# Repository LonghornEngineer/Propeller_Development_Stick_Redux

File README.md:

***
###Propeller_Development_Stick_Redux
***
**Tiny development board based on the Parallax Propeller.**

More information can be found on the [Propeller Development Stick project page](http://longhornengineer.com/projects/pcb/propeller-development-stick-redux/).

Board Files are for Cadsoft Eagle V6.0+

***
**License Information**

This project is under the [Creative Commons Attribution-ShareAlike 4.0 International License](LICENSE.md). These files are provided with no warranty and should be used at your own risk. 

***

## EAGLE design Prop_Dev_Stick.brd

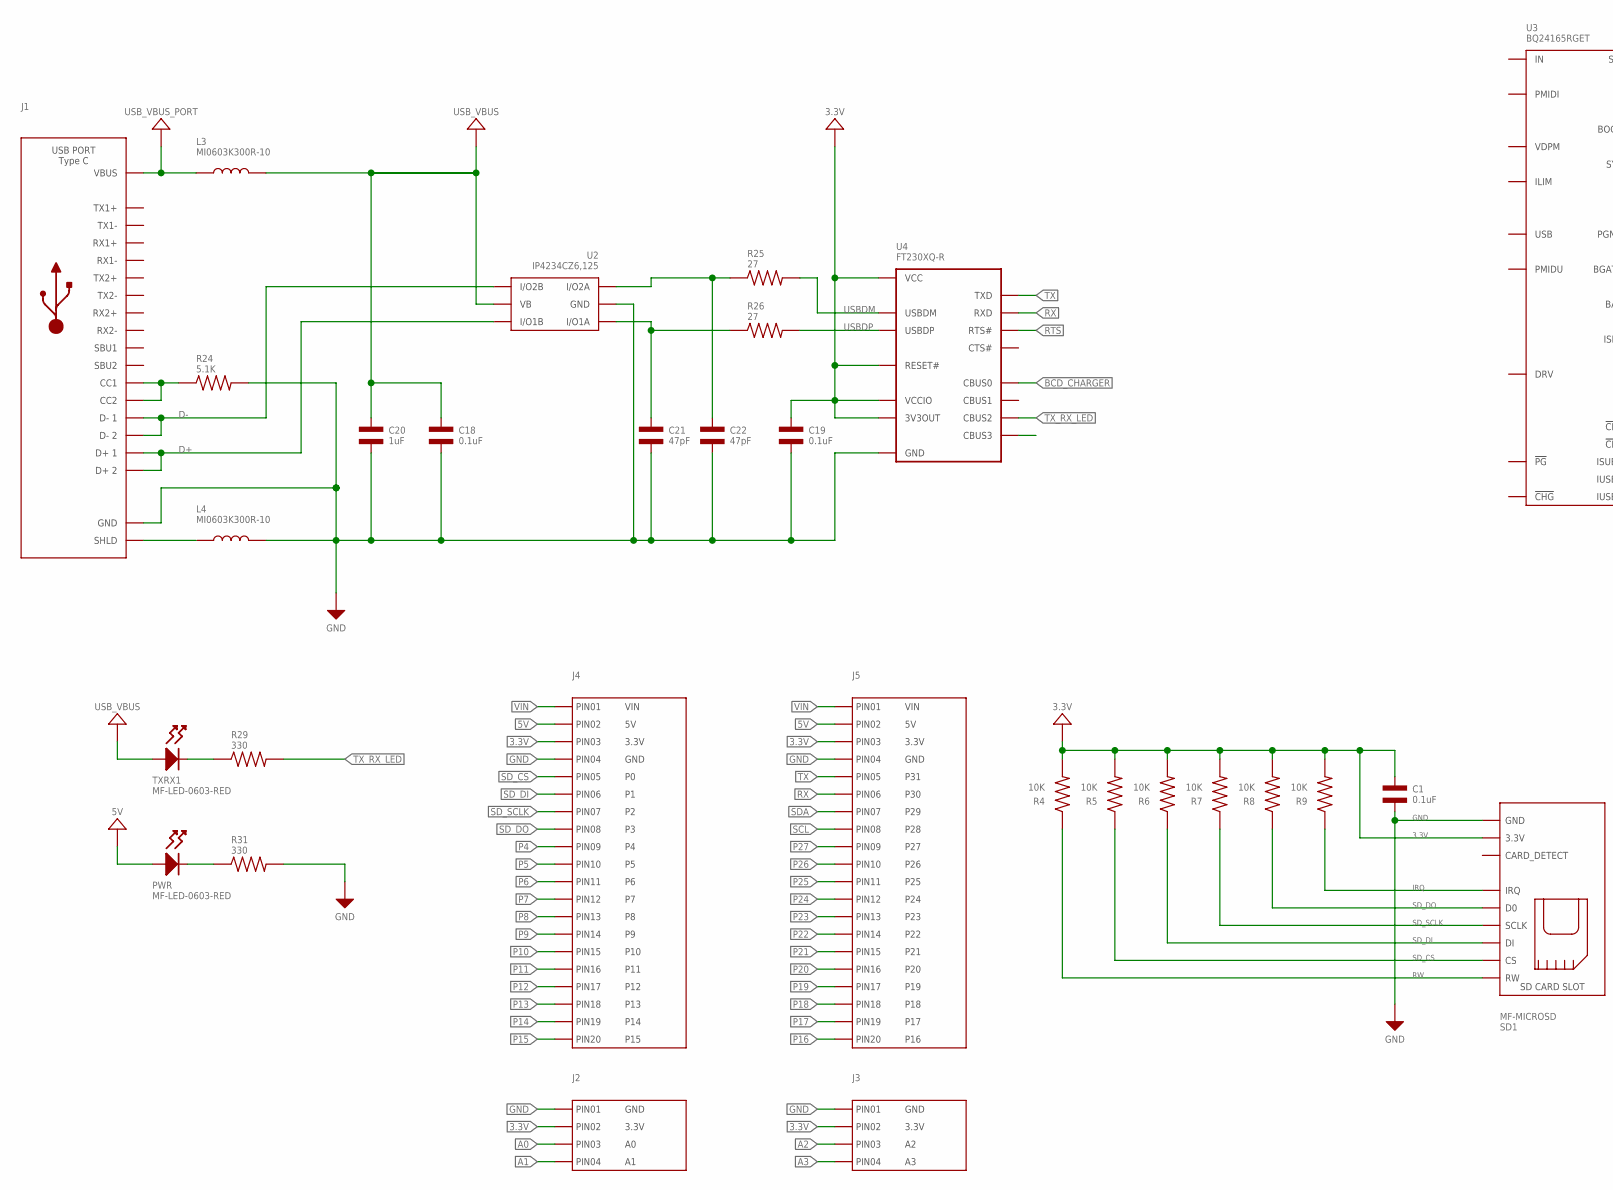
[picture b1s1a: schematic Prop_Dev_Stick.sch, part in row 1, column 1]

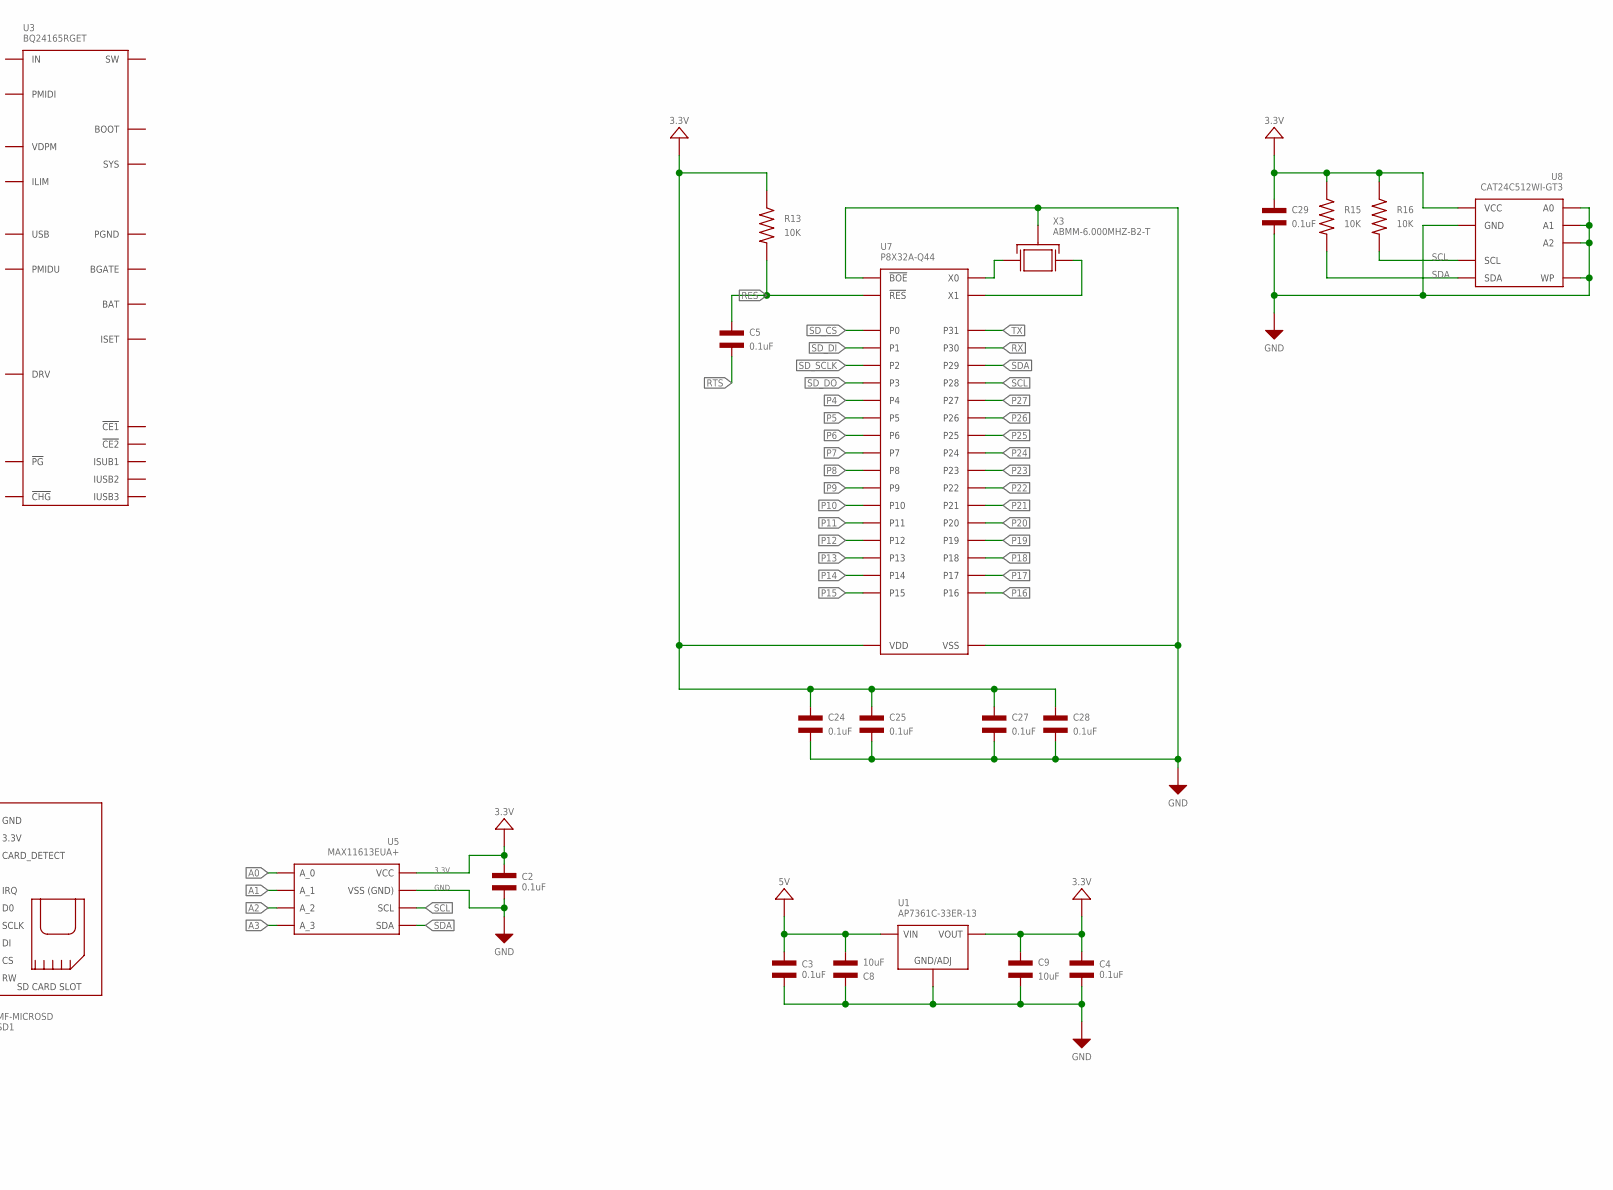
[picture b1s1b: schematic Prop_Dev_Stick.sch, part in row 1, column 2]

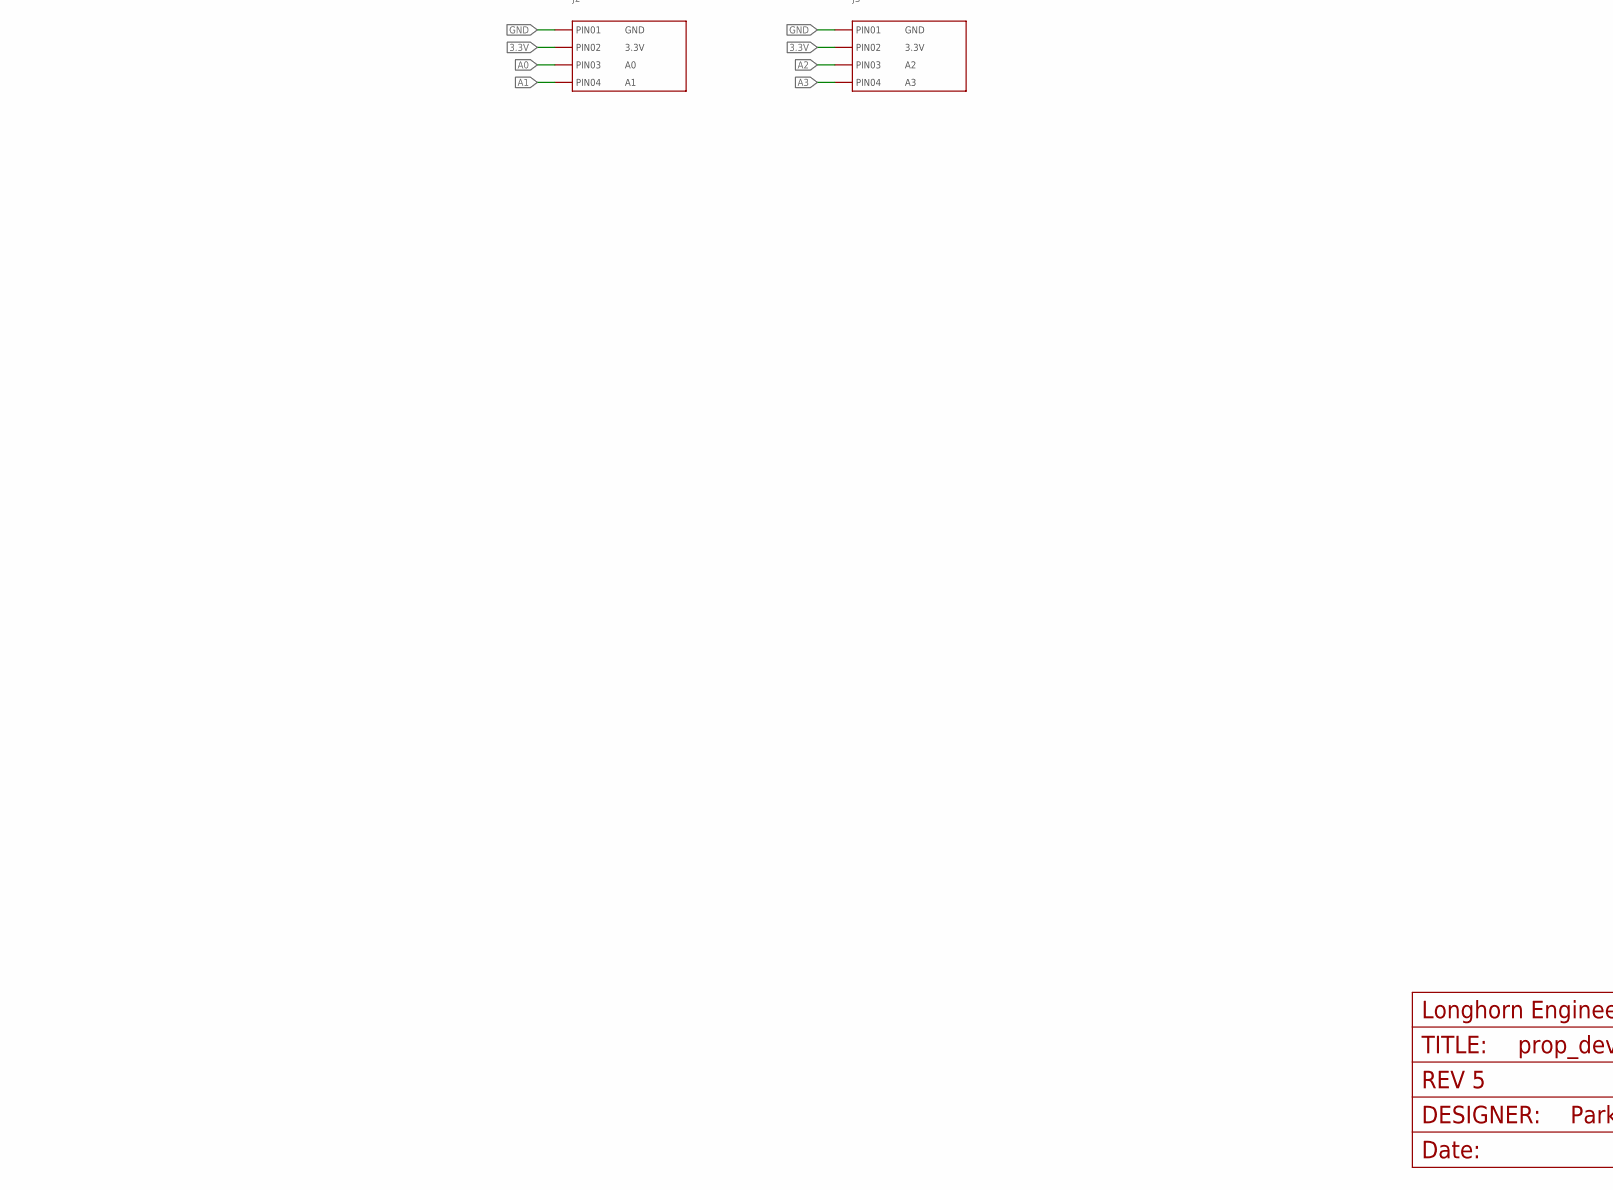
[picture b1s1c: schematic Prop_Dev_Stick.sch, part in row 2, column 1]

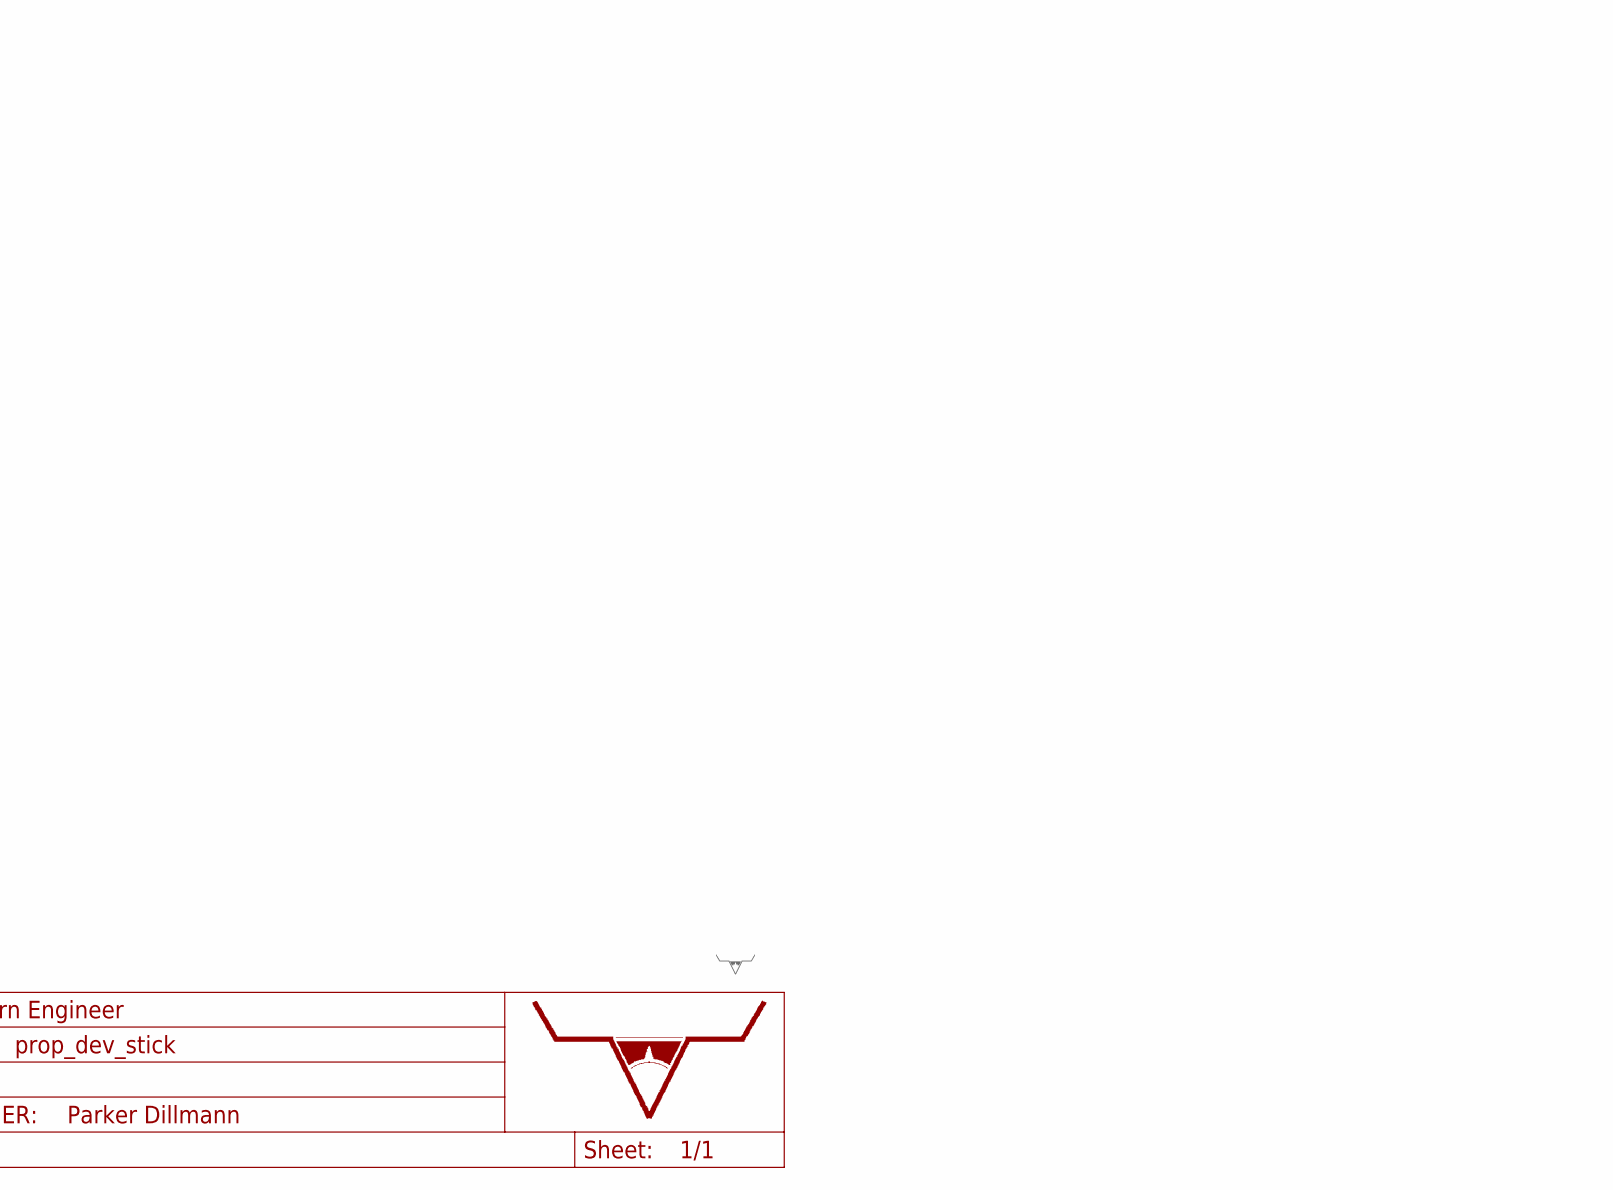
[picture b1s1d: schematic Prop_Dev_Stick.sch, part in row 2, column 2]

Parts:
C1, C2, C3, C4, C18, C19: 0.1uF; C0603
C5, C24, C25, C27, C28, C29: 0.1uF; C0402; MPN MF-CAP-0603-0.1uF
C8, C9: 10uF; C1206
C20: 1uF; C0603
C21, C22: 47pF; C0603
J1: USB_TYPE-C_105450-0101; 105450-0101
J2, J3: CON_01X04_2.54MM_PIN_HEADER; 2.54MM_01X04_PIN_HEADER
J4, J5: CON_01X20_2.54MM_PIN_HEADER; 2.54MM_01X20_PIN_HEADER
L3, L4: MI0603K300R-10; L0603
PWR: MF-LED-0603-RED; LED0603
R4, R5, R6, R7, R8, R9: 10K; R0603
R13: 10K; R0402; MPN MF-RES-0805-10K
R15, R16: 10K; R0402; MPN MF-RES-0603-10K
R24: 5.1K; R0603
R25, R26: 27; R0603
R29, R31: 330; R0402
SD1: MF-MICROSD
TXRX1: MF-LED-0603-RED; LED0603
U1: AP7361C-33ER-13; ADP3338_SOT-223-3
U2: IP4234CZ6,125; IP4234CZ6_SOT-457-6
U3: BQ24165RGET; BQ24165_QFN-24
U4: FT230XQ-R; FT230X_QFN-16
U5: MAX11613EUA+; MAX11613_UMAX-8
U7: P8X32A-Q44; P8X32A_QFN-44; MPN P8X32A-Q44
U8: CAT24C512WI-GT3; SOIC-8_W; MPN CAT24C512WI-GT3
U$1: LHE_FRAME
U$2: LHE_LOGOLHE_LOGO; LHE_LOGO
X3: ABMM-6.000MHZ-B2-T; 7MMX5MM; MPN ABMM-6.000MHZ-B2-T

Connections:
3.3V: C1.P$1, C2.P$1, C4.P$1, C9.P$1, C19.P$1, C24.P$1, C25.P$1, C27.P$1, C28.P$1, C29.P$1, J2.2, J3.2, J4.3, J5.3, R4.P$2, R5.P$2, R6.P$2, R7.P$2, R8.P$2, R9.P$2, R13.P$1, R15.P$1, R16.P$1, SD1.PIN4 (3.3V), U1.2 (OUT), U1.PAD (OUT), U4.1 (VCCIO), U4.8 (3V3OUT), U4.9 (RESET#), U4.10 (VCC), U5.P$8 (VCC), U7.8 (VDD), U7.18 (VDD), U7.30 (VDD), U7.40 (VDD), U8.8 (VCC)
5V: C3.P$1, C8.P$2, J4.2, J5.2, PWR.ANODE, U1.3 (IN)
A0: J2.3, U5.P$1 (A_0)
A1: J2.4, U5.P$2 (A_1)
A2: J3.3, U5.P$3 (A_2)
A3: J3.4, U5.P$4 (A_3)
BCD_CHARGER: U4.12 (CBUS0)
CC1/1: J1.A5 (CC1), J1.B5 (CC2), R24.P$1
D+: J1.A6 (D+1), J1.B6 (D+2), U2.3 (I/O1B)
D-: J1.A7 (D-1), J1.B7 (D-2), U2.4 (I/O2B)
GND: C1.P$2, C2.P$2, C3.P$2, C4.P$2, C8.P$1, C9.P$2, C18.P$2, C19.P$2, C20.P$2, C21.P$2, C22.P$2, C24.P$2, C25.P$2, C27.P$2, C28.P$2, C29.P$2, J1.A1 (GND), J1.A12 (GND), J1.B1 (GND), J1.B12 (GND), J2.1, J3.1, J4.4, J5.4, L4.P$2, R24.P$2, R31.P$2, SD1.G0 (GND), SD1.G1 (GND), SD1.PIN6 (GND), U1.1 (GND), U2.2 (GND), U4.3 (GND), U4.13 (GND), U4.PAD (GND), U5.P$7 (GND), U7.5 (VSS), U7.6 (!BOE), U7.17 (VSS), U7.27 (VSS), U7.39 (VSS), U8.1 (A0), U8.2 (A1), U8.3 (A2), U8.4 (GND), U8.7 (WP), X3.P$2 (GND), X3.P$4 (GND)
IRQ: R9.P$1, SD1.PIN8 (IRQ)
unnamed: R29.P$1, TXRX1.CATHODE
unnamed: PWR.CATHODE, R31.P$1
unnamed: J1.S_T1 (SHLD), J1.S_T2 (SHLD), J1.S_T3 (SHLD), J1.S_T4 (SHLD), L4.P$1
unnamed: C21.P$1, R26.P$1, U2.1 (I/O1A)
unnamed: C22.P$1, R25.P$1, U2.6 (I/O2A)
P4: J4.9, U7.1 (P4)
P5: J4.10, U7.2 (P5)
P6: J4.11, U7.3 (P6)
P7: J4.12, U7.4 (P7)
P8: J4.13, U7.9 (P8)
P9: J4.14, U7.10 (P9)
P10: J4.15, U7.11 (P10)
P11: J4.16, U7.12 (P11)
P12: J4.17, U7.13 (P12)
P13: J4.18, U7.14 (P13)
P14: J4.19, U7.15 (P14)
P15: J4.20, U7.16 (P15)
P16: J5.20, U7.19 (P16)
P17: J5.19, U7.20 (P17)
P18: J5.18, U7.21 (P18)
P19: J5.17, U7.22 (P19)
P20: J5.16, U7.23 (P20)
P21: J5.15, U7.24 (P21)
P22: J5.14, U7.25 (P22)
P23: J5.13, U7.26 (P23)
P24: J5.12, U7.31 (P24)
P25: J5.11, U7.32 (P25)
P26: J5.10, U7.33 (P26)
P27: J5.9, U7.34 (P27)
RES: C5.P$1, R13.P$2, U7.7 (!RES)
RTS: C5.P$2, U4.16 (RTS#)
RW: R4.P$1, SD1.PIN1 (RW)
RX: J5.6, U4.2 (RXD), U7.37 (P30)
SCL: J5.8, R16.P$2, U5.P$5 (SCL), U7.35 (P28), U8.6 (SCL)
SDA: J5.7, R15.P$2, U5.P$6 (SDA), U7.36 (P29), U8.5 (SDA)
SD_CS: J4.5, R5.P$1, SD1.PIN2 (CS), U7.41 (P0)
SD_DI: J4.6, R6.P$1, SD1.PIN3 (DI), U7.42 (P1)
SD_DO: J4.8, R8.P$1, SD1.PIN7 (D0), U7.44 (P3)
SD_SCLK: J4.7, R7.P$1, SD1.PIN5 (SCLK), U7.43 (P2)
TX: J5.5, U4.15 (TXD), U7.38 (P31)
TX_RX_LED: R29.P$2, U4.5 (CBUS2)
USBDM: R25.P$2, U4.7 (USBDM)
USBDP: R26.P$2, U4.6 (USBDP)
USB_VBUS: C18.P$1, C20.P$1, L3.P$2, TXRX1.ANODE, U2.5 (VB)
USB_VBUS_PORT: J1.A4 (VBUS), J1.A9 (VBUS), J1.B4 (VBUS), J1.B9 (VBUS), L3.P$1
VIN: J4.1, J5.1
X4: U7.29 (X0), X3.P$3 (X1)
X5: U7.28 (X1), X3.P$1 (X0)

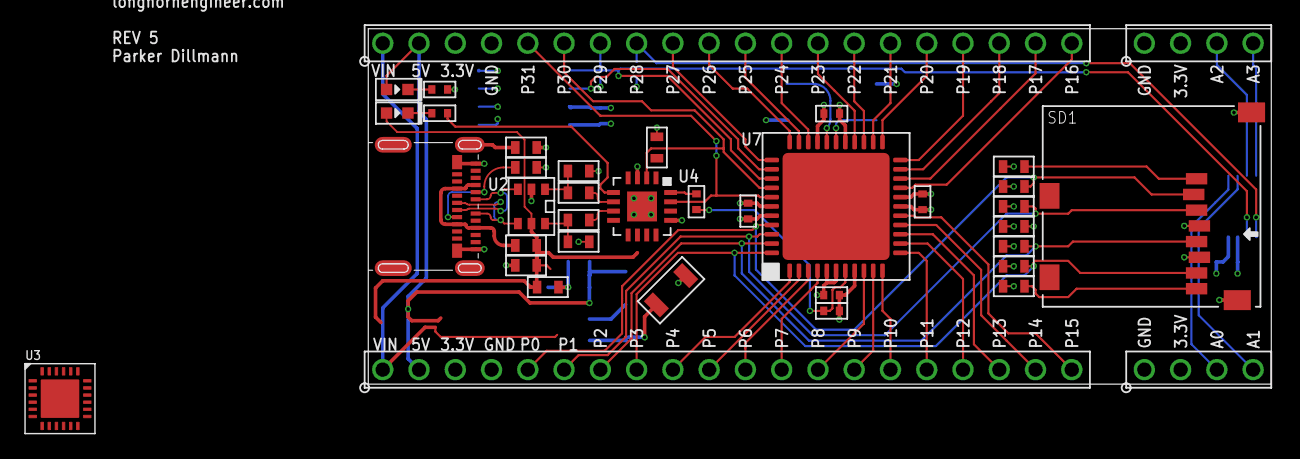
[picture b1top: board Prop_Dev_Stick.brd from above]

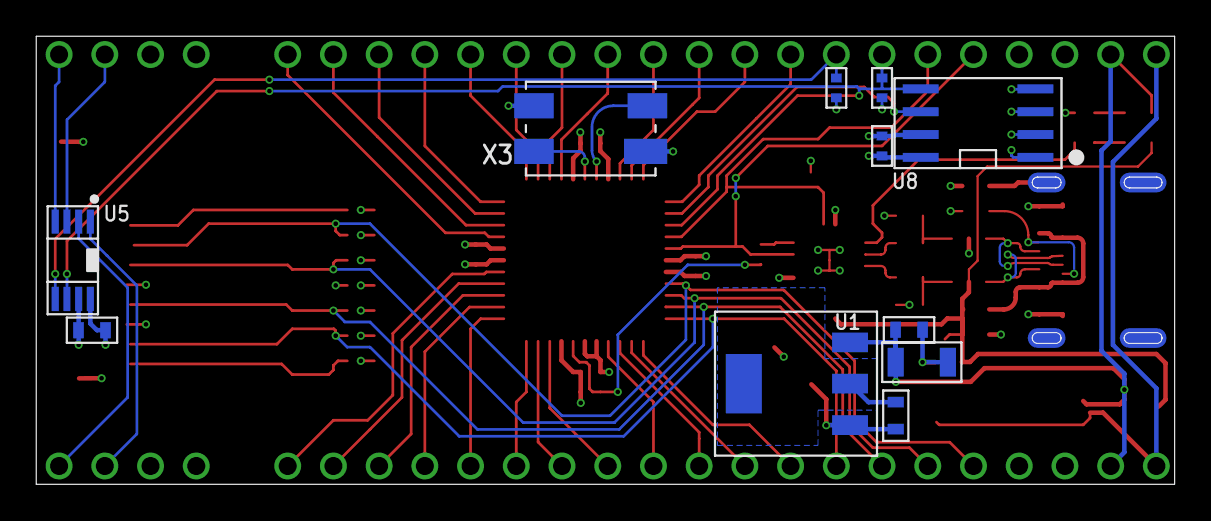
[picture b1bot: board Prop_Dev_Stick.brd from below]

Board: 4 copper layers, 63.2 x 24.9 mm, 51 parts (11 on the bottom side), 59 nets.

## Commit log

2013-10-22 Push of REV_2 files
2013-10-22 REV_0B push
2013-10-22 Push Rev 1
2013-10-22 Added FT230X FTProg Template
2013-10-28 Added template for FT230X to ignore enumeration
2013-12-04 Added PropGcc Template files
2013-12-04 Added readme for FT230X FT-Prog.
2013-12-04 Fixed Values on a couple parts. Added BOM.txt
2013-12-04 added description for board files.
2013-12-04 Changed silkscreen error.
2013-12-05 Added PDS_Panel
2013-12-16 Adjusted edge of board to remove DRC issues.
2014-01-21 Uploading Schematic.png
2014-04-09 Update to CC-BY-SA License.
2014-11-07 Removing Panel files.
2014-11-07 Finished REV3!!!
2014-12-16 Added power switching for LDO Voltage Dropout.
2014-12-17 Changed SD Card Slot.
2014-12-17 Changed USB connector
2014-12-22 Routed power switching for LDO dropout
2014-12-23 Changed crystal.
2014-12-28 REV 4 push
    New SD Card, MAX ADC, added 10uF cap.
2014-12-29 Added paste to USB connector shield hole.
2015-01-13 Fixed readme
2015-12-17 Updated design to use latest library style!
2015-12-17 Updated to REV 4B
2016-02-17 REV 4B
2016-08-23 new readme
2019-01-15 Working on REV5
    REV5 will feature 0402 parts, QFN Prop, USB Type-C, and a host of other
    small changes.
2024-07-03 pushing updates from long ago

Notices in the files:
parts and their libraries:
PP_Aesthetics: (c) 2013 Longhorn Engineer
PP_Aesthetics: (c) 2018 Longhorn Engineer
